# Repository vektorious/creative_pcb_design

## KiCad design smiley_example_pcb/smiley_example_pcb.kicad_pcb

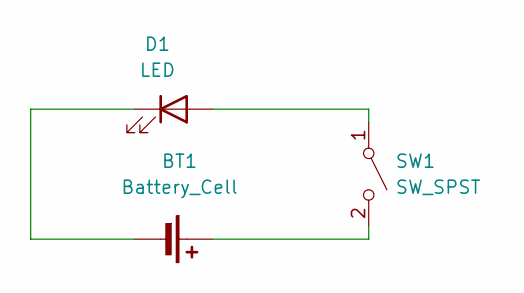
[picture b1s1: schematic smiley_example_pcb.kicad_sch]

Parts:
BT1: Battery_Cell; BatteryHolder_Keystone_3034_1x20mm
D1: LED; LED_D5.0mm
SW1: SW_SPST; PinHeader_1x02_P2.54mm_Vertical

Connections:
unnamed: BT1.1 (+), SW1.2 (B)
unnamed: BT1.2 (-), D1.1 (K)
unnamed: D1.2 (A), SW1.1 (A)

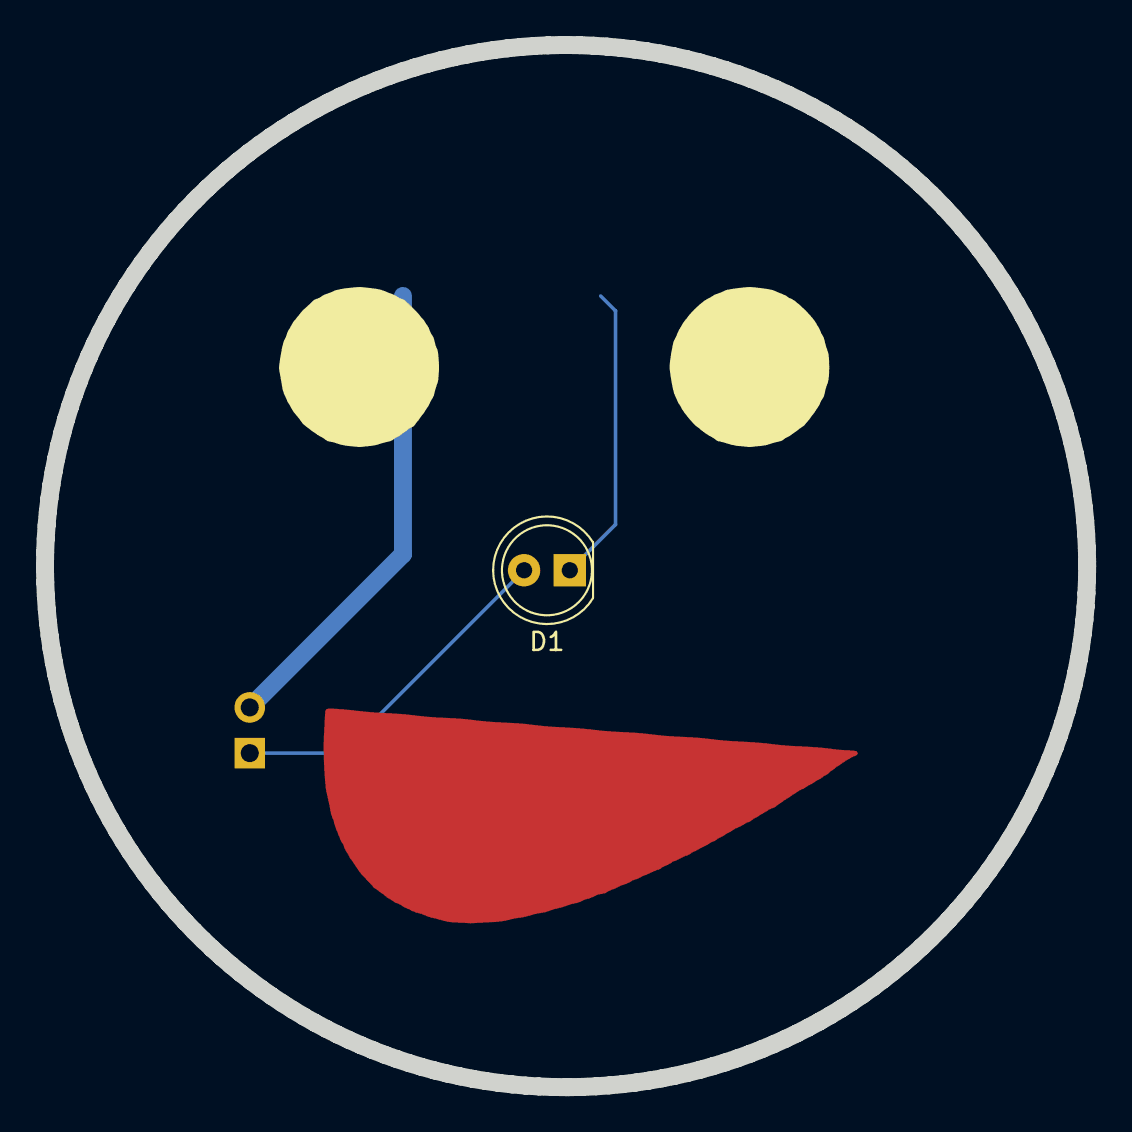
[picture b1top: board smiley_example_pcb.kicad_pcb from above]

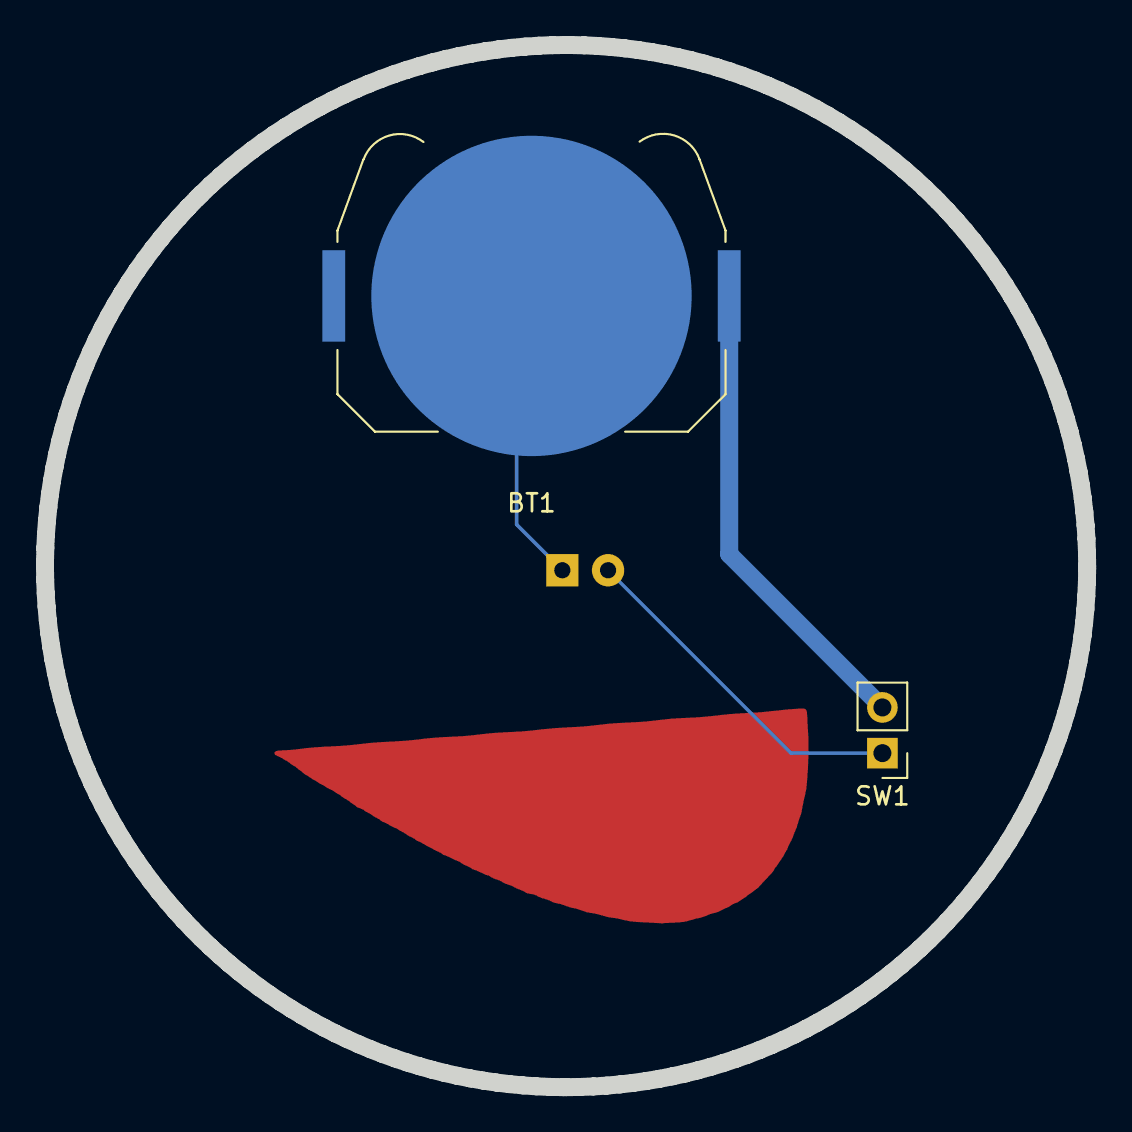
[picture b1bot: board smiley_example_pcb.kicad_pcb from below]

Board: 2 copper layers, 57.9 x 57.9 mm, 3 parts (2 on the bottom side), 3 nets.

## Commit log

2025-05-08 upload
